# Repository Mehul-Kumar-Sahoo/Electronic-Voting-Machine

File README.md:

# Electronic Voting Machine (EVM)

Skills: Proteus 7, Digital Electronics

- I am Mehul Kumar Sahoo of in B.Tech Part 2 in IIT (BHU), Varanasi persuing Electronics Engineering. 
- I have made an Electronic Voting Machine (EVM) using PROTEUS for the event of DIGISIM in Udyam'23, annual technical fest of Electronics Engineering Society IIT (BHU), Varanasi.
- I have also designed a PCB using EagleCAD to implement the EVM (Schematic, Board and Gerber files are also attached in this repository).

## Features
 1) A start button to begin the voting process for a voter giving them a window of 15 seconds to vote for a person.

 2) After each voting button is pressed, the circuit stops working for 3 seconds to prevent devouncing of a button.

 3) A count button which when pressed counts the number of votes the winning person has.
 4) 7-segment displays to display the winning candidate, the number of votes for winning candidate, and the time left for voting.

## PCB Design (Made using EagleCAD)
### Top Layer

### Bottom Layer

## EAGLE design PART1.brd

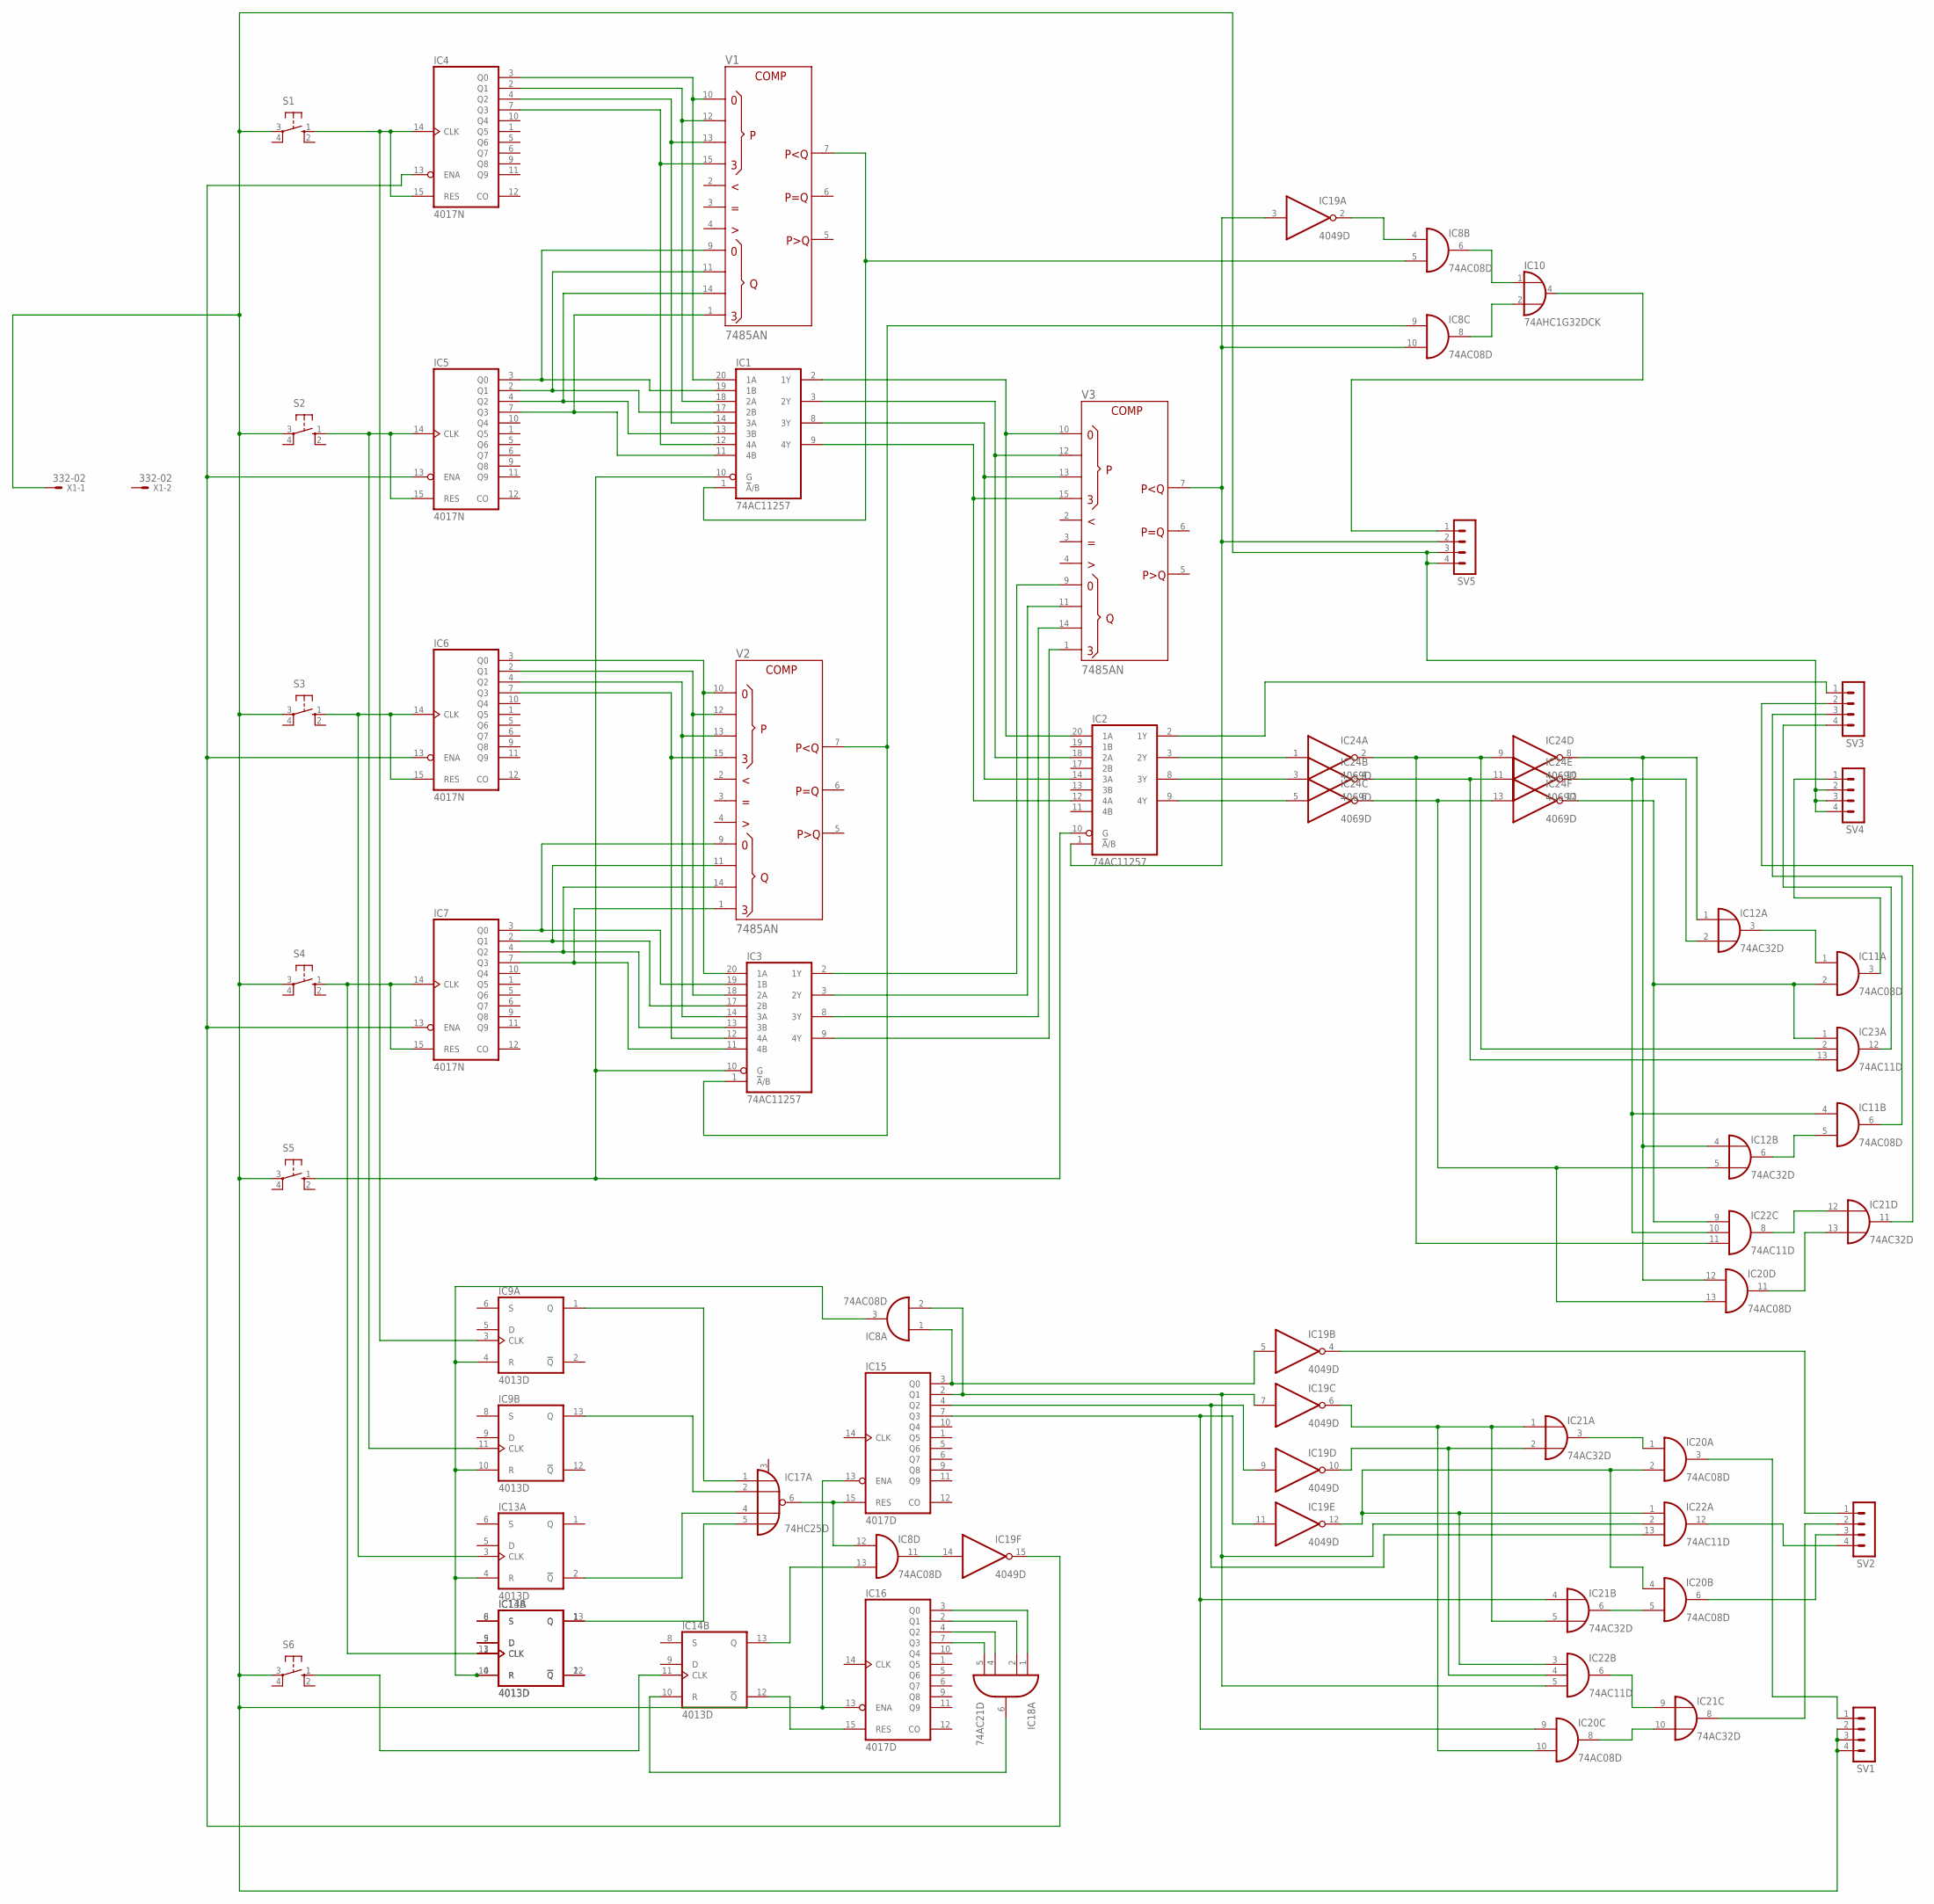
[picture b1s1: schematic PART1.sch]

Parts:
IC1, IC2, IC3: 74AC11257; DIL20
IC4, IC5, IC6, IC7: 4017N; DIL16
IC8, IC11, IC20: 74AC08D; SO14
IC9, IC13, IC14: 4013D; SO14
IC10: 74AHC1G32DCK; SC70-5
IC12, IC21: 74AC32D; SO14
IC15, IC16: 4017D; SO16
IC17: 74HC25D; SO14
IC18: 74AC21D; SO14
IC19: 4049D; SO16
IC22, IC23: 74AC11D; SO14
IC24: 4069D; SO14
S1, S2, S3, S4, S5, S6: 10-XX; B3F-10XX
SV1, SV2, SV3, SV4, SV5: MA04-1
V1, V2, V3: 7485AN; DIL16
X1: 332-02

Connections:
+UB: V1.16 (+UB), V2.16 (+UB), V3.16 (+UB)
-UB: V1.8 (-UB), V2.8 (-UB), V3.8 (-UB)
GND: IC1.4 (GND), IC1.5 (GND), IC1.6 (GND), IC1.7 (GND), IC2.4 (GND), IC2.5 (GND), IC2.6 (GND), IC2.7 (GND), IC3.4 (GND), IC3.5 (GND), IC3.6 (GND), IC3.7 (GND), IC8.7 (GND), IC10.3 (GND), IC11.7 (GND), IC12.7 (GND), IC17.7 (GND), IC18.7 (GND), IC20.7 (GND), IC21.7 (GND), IC22.7 (GND), IC23.7 (GND)
unnamed: IC13.2 (!Q), IC17.4 (I2)
unnamed: IC1.20 (1A), IC4.3 (Q0), V1.10 (P0)
unnamed: IC5.14 (CLK), IC5.15 (RES), IC9.11 (CLK), S2.1 (S)
unnamed: IC6.14 (CLK), IC6.15 (RES), IC13.3 (CLK), S3.1 (S)
unnamed: IC1.18 (2A), IC4.2 (Q1), V1.12 (P1)
unnamed: IC1.14 (3A), IC4.4 (Q2), V1.13 (P2)
unnamed: IC4.13 (ENA), IC5.13 (ENA), IC6.13 (ENA), IC7.13 (ENA), IC19.15 (O)
unnamed: IC1.12 (4A), IC4.7 (Q3), V1.15 (P3)
unnamed: IC1.19 (1B), IC5.3 (Q0), V1.9 (Q0)
unnamed: IC1.17 (2B), IC5.2 (Q1), V1.11 (Q1)
unnamed: IC1.13 (3B), IC5.4 (Q2), V1.14 (Q2)
unnamed: IC1.11 (4B), IC5.7 (Q3), V1.1 (Q3)
unnamed: IC3.11 (4B), IC7.7 (Q3), V2.1 (Q3)
unnamed: IC1.10 (G), IC2.10 (G), IC3.10 (G), S5.1 (S)
unnamed: IC1.2 (1Y), IC2.20 (1A), V3.10 (P0)
unnamed: IC1.3 (2Y), IC2.18 (2A), V3.12 (P1)
unnamed: IC3.20 (1A), IC6.3 (Q0), V2.10 (P0)
unnamed: IC3.18 (2A), IC6.2 (Q1), V2.12 (P1)
unnamed: IC3.14 (3A), IC6.4 (Q2), V2.13 (P2)
unnamed: IC3.12 (4A), IC6.7 (Q3), V2.15 (P3)
unnamed: IC3.19 (1B), IC7.3 (Q0), V2.9 (Q0)
unnamed: IC3.17 (2B), IC7.2 (Q1), V2.11 (Q1)
unnamed: IC3.13 (3B), IC7.4 (Q2), V2.14 (Q2)
unnamed: IC1.8 (3Y), IC2.14 (3A), V3.13 (P2)
unnamed: IC2.1 (!A!/B), IC8.10 (I1), IC19.3 (I), SV5.2, V3.7 (PLTQ)
unnamed: IC3.9 (4Y), V3.1 (Q3)
unnamed: IC3.8 (3Y), V3.14 (Q2)
unnamed: IC3.3 (2Y), V3.11 (Q1)
unnamed: IC1.1 (!A!/B), IC8.5 (I1), V1.7 (PLTQ)
unnamed: IC3.1 (!A!/B), IC8.9 (I0), V2.7 (PLTQ)
unnamed: IC3.2 (1Y), V3.9 (Q0)
unnamed: IC8.4 (I0), IC19.2 (O)
unnamed: IC8.8 (O), IC10.2 (I1)
unnamed: IC8.6 (O), IC10.1 (I0)
unnamed: IC10.4 (O), SV5.1
unnamed: IC1.9 (4Y), IC2.12 (4A), V3.15 (P3)
unnamed: IC22.11 (I2), IC23.2 (I1), IC24.2 (O), IC24.9 (I)
unnamed: IC23.13 (I2), IC24.4 (O), IC24.11 (I)
unnamed: IC12.5 (I1), IC20.13 (I1), IC24.6 (O), IC24.13 (I)
unnamed: IC12.1 (I0), IC12.4 (I0), IC20.12 (I0), IC24.8 (O)
unnamed: IC2.9 (4Y), IC24.5 (I)
unnamed: IC2.8 (3Y), IC24.3 (I)
unnamed: IC2.3 (2Y), IC24.1 (I)
unnamed: IC2.2 (1Y), SV3.1
unnamed: IC11.2 (I1), IC22.9 (I0), IC23.1 (I0), IC24.12 (O)
unnamed: IC11.1 (I0), IC12.3 (O)
unnamed: IC11.3 (O), SV4.1
unnamed: IC13.13 (Q), IC14.1 (Q)
unnamed: IC13.12 (!Q), IC14.2 (!Q)
unnamed: IC7.14 (CLK), IC7.15 (RES), IC13.11 (CLK), IC14.3 (CLK), S4.1 (S)
unnamed: IC8.3 (O), IC9.4 (R), IC9.10 (R), IC13.4 (R), IC13.10 (R), IC14.4 (R)
unnamed: IC13.9 (D), IC14.5 (D)
unnamed: IC13.8 (S), IC14.6 (S)
unnamed: IC8.1 (I0), IC15.3 (Q0), IC19.5 (I)
unnamed: IC8.2 (I1), IC15.2 (Q1), IC19.7 (I), IC22.2 (I1), IC22.5 (I2)
unnamed: IC15.13 (ENA), IC16.13 (ENA), S1.3, S2.3, S3.3, S4.3, S5.3, S6.3, SV1.2, SV1.3, SV1.4, SV4.2, SV4.3, SV4.4, SV5.3, SV5.4, X1.1
unnamed: IC9.1 (Q), IC17.1 (I0)
unnamed: IC9.13 (Q), IC17.2 (I1)
unnamed: IC8.12 (I0), IC15.15 (RES), IC17.6 (O)
unnamed: IC16.3 (Q0), IC18.1 (I0)
unnamed: IC16.2 (Q1), IC18.2 (I1)
unnamed: IC16.4 (Q2), IC18.4 (I2)
unnamed: IC16.7 (Q3), IC18.5 (I3)
unnamed: IC14.10 (R), IC18.6 (O)
unnamed: IC8.13 (I1), IC14.13 (Q)
unnamed: IC14.11 (CLK), S6.1 (S)
unnamed: IC14.12 (!Q), IC16.15 (RES)
unnamed: IC15.4 (Q2), IC19.9 (I), IC22.13 (I2)
unnamed: IC15.7 (Q3), IC19.11 (I), IC20.9 (I0), IC21.4 (I0)
unnamed: IC8.11 (O), IC19.14 (I)
unnamed: IC19.6 (O), IC20.10 (I1), IC21.1 (I0), IC21.5 (I1)
unnamed: IC4.14 (CLK), IC4.15 (RES), IC9.3 (CLK), S1.1 (S)
unnamed: IC19.10 (O), IC21.2 (I1), IC22.4 (I1)
unnamed: IC20.1 (I0), IC21.3 (O)
unnamed: IC19.12 (O), IC20.2 (I1), IC20.4 (I0), IC22.1 (I0), IC22.3 (I0)
unnamed: IC19.4 (O), SV2.1
unnamed: IC21.8 (O), SV2.2
unnamed: IC20.6 (O), SV2.3
unnamed: IC22.12 (O), SV2.4
unnamed: IC20.5 (I1), IC21.6 (O)
unnamed: IC21.9 (I0), IC22.6 (O)
unnamed: IC20.8 (O), IC21.10 (I1)
unnamed: IC20.3 (O), SV1.1
unnamed: IC23.12 (O), SV3.4
unnamed: IC11.5 (I1), IC12.6 (O)
unnamed: IC11.6 (O), SV3.3
unnamed: IC21.12 (I0), IC22.8 (O)
unnamed: IC20.11 (O), IC21.13 (I1)
unnamed: IC11.4 (I0), IC12.2 (I1), IC22.10 (I1), IC24.10 (O)
unnamed: IC21.11 (O), SV3.2
VCC: IC1.15 (VCC), IC1.16 (VCC), IC2.15 (VCC), IC2.16 (VCC), IC3.15 (VCC), IC3.16 (VCC), IC8.14 (VCC), IC10.5 (VCC), IC11.14 (VCC), IC12.14 (VCC), IC17.14 (VCC), IC18.14 (VCC), IC20.14 (VCC), IC21.14 (VCC), IC22.14 (VCC), IC23.14 (VCC)
VDD: IC4.16 (VDD), IC5.16 (VDD), IC6.16 (VDD), IC7.16 (VDD), IC9.14 (VDD), IC13.14 (VDD), IC14.14 (VDD), IC15.16 (VDD), IC16.16 (VDD), IC19.1 (VDD), IC24.14 (VDD)
VSS: IC4.8 (VSS), IC5.8 (VSS), IC6.8 (VSS), IC7.8 (VSS), IC9.7 (VSS), IC13.7 (VSS), IC14.7 (VSS), IC15.8 (VSS), IC16.8 (VSS), IC19.8 (VSS), IC24.7 (VSS)

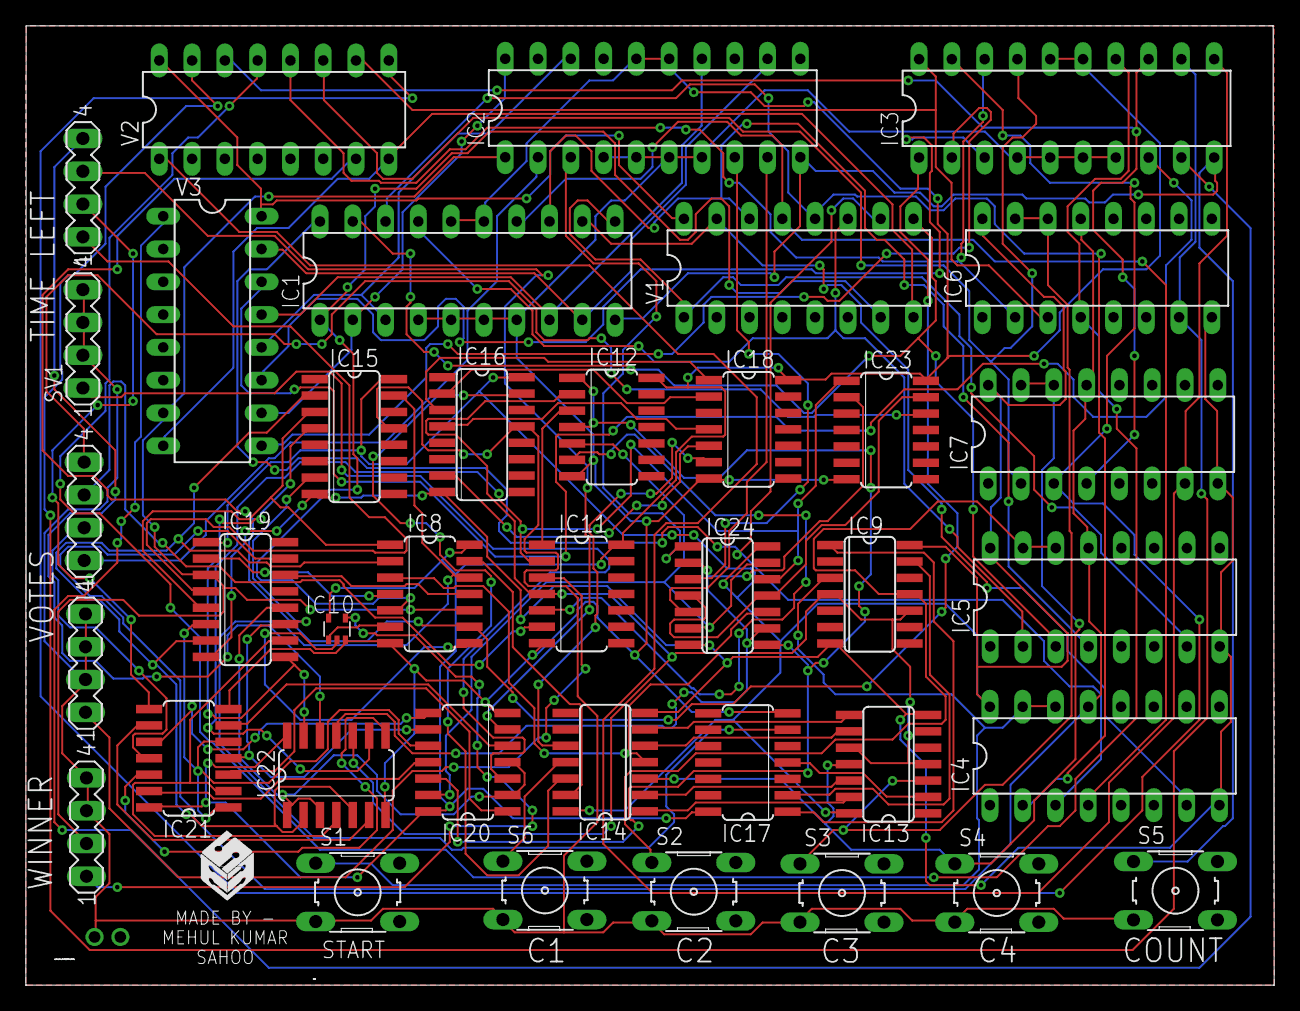
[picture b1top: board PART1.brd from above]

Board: 2 copper layers, 96.7 x 74.3 mm, 39 parts (1 on the bottom side), 96 nets.

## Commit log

2023-05-16 Adding all the files
